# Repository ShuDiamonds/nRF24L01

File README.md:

# nRF24L01
Wireless connection between Arduino and Raspberry pi 3 using nRF24L01

ref:http://invent.module143.com/daskal_tutorial/raspberry-pi-3-wireless-pi-to-arduino-communication-with-nrf24l01/

https://ehbtj.com/electronics/nrf24l01/

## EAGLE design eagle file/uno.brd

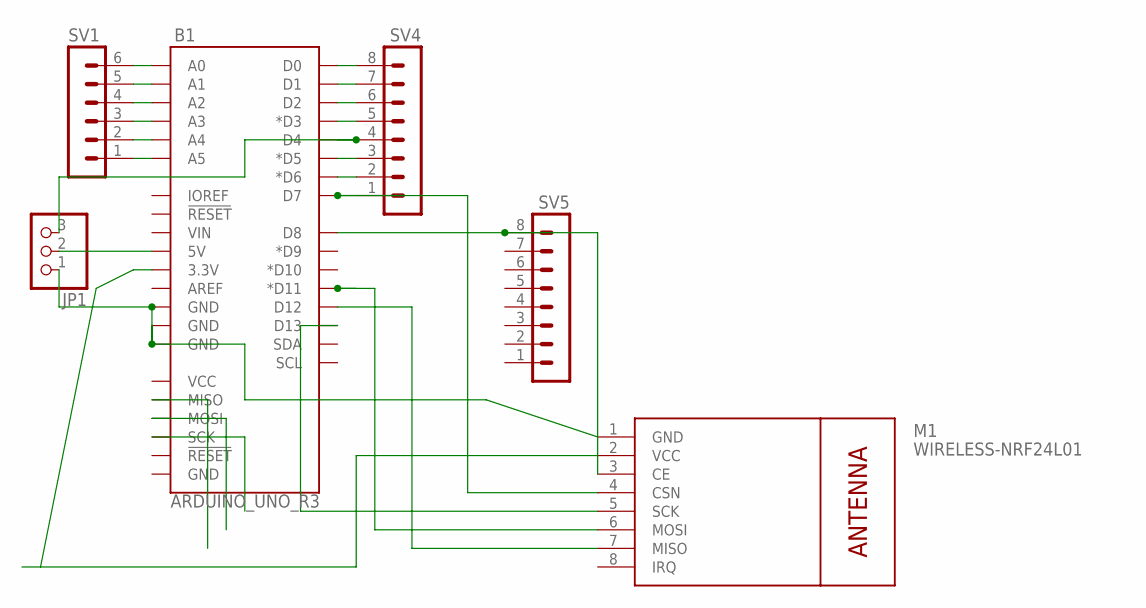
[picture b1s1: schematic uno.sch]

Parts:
B1: ARDUINO_UNO_R3; ARDUINO_R3
JP1: PINHD-1X3; 1X03
M1: WIRELESS-NRF24L01
SV1: MA06-1
SV4, SV5: MA08-1

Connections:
unnamed: B1.A5, SV1.1
unnamed: B1.A4, SV1.2
unnamed: B1.A3, SV1.3
unnamed: B1.A2, SV1.4
unnamed: B1.A1, SV1.5
unnamed: B1.A0, SV1.6
unnamed: B1.3.3V, M1.2 (VCC)
unnamed: B1.D13, M1.5 (SCK)
unnamed: B1.D11 (*D11), M1.6 (MOSI)
unnamed: B1.D12, M1.7 (MISO)
unnamed: B1.5V, JP1.2
unnamed: B1.GND@2 (GND), B1.GND@3 (GND), B1.GND@4 (GND), JP1.1, M1.1 (GND)
unnamed: B1.D8, M1.3 (CE), SV5.8
unnamed: B1.D7, M1.4 (CSN), SV4.1
unnamed: B1.D6 (*D6), SV4.2
unnamed: B1.D5 (*D5), SV4.3
unnamed: B1.D4, JP1.3, SV4.4
unnamed: B1.D3 (*D3), SV4.5
unnamed: B1.D2, SV4.6
unnamed: B1.D1, SV4.7
unnamed: B1.D0, SV4.8

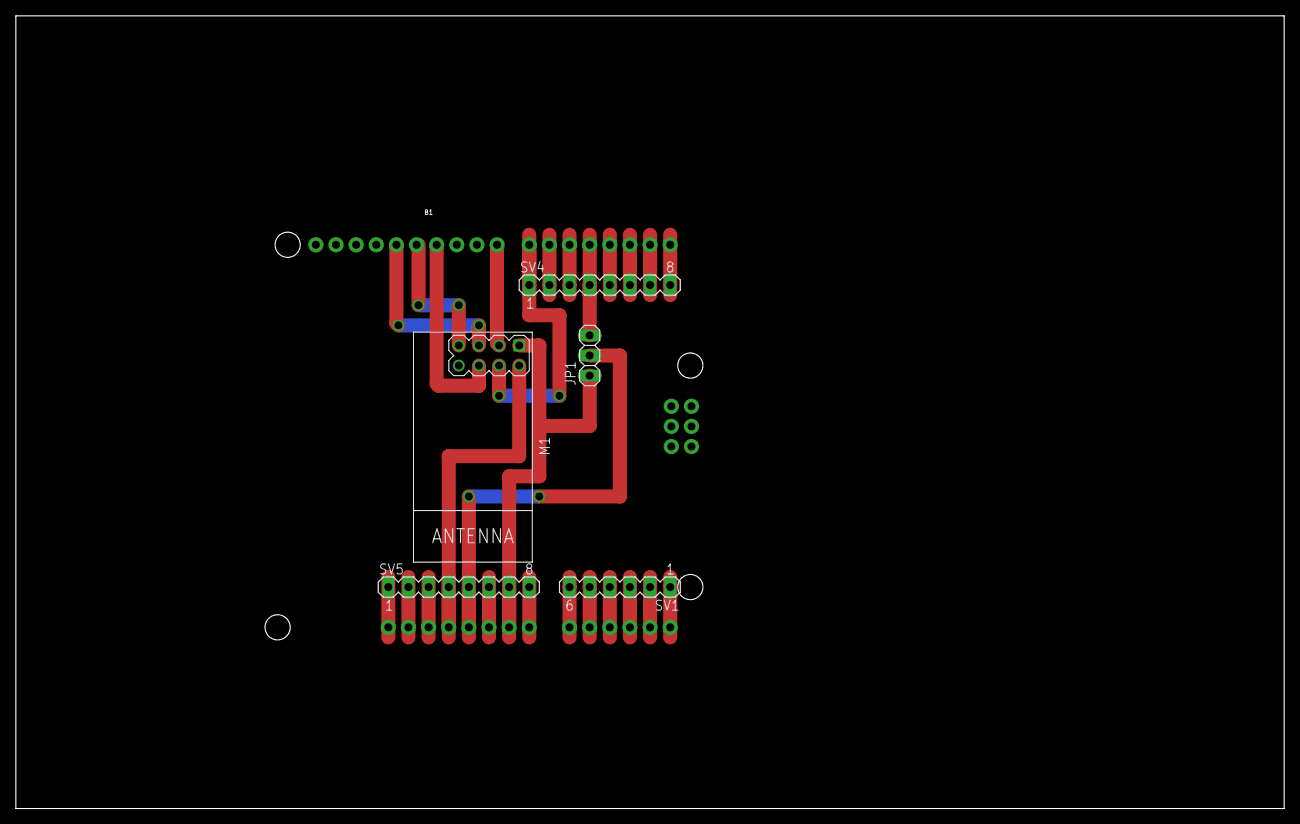
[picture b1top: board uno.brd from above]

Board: 2 copper layers, 160.0 x 100.0 mm, 6 parts (0 on the bottom side), 21 nets.

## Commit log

2019-01-19 review2
2019-01-20 add file
2019-01-20 add files
2019-01-26 reviewed

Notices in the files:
parts and their libraries:
Arduino: Licensing: Creative Commons ShareAlike 4.0 International - https://creativecommons.org/licenses/by-sa/4.0
diy-modules: Released under the Creative Commons Attribution 4.0 International License: http://creativecommons.org/licenses/by/4.0
